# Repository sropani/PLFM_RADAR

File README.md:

# AERIS-10: Open Source Pulse Linear Frequency Modulated Phased Array Radar

AERIS-10 is an open-source, low-cost 10.5 GHz phased array radar system featuring Pulse Linear Frequency Modulated (LFM) modulation. Available in two versions (3km and 20km range), it's designed for researchers, drone developers, and serious SDR enthusiasts who want to explore and experiment with phased array radar technology.

## 📡 Overview

The AERIS-10 project aims to democratize radar technology by providing a fully open-source, modular, and hackable radar system. Whether you're a university researcher, a drone startup, or an advanced maker, AERIS-10 offers a platform for experimenting with beamforming, pulse compression, Doppler processing, and target tracking.

## 🔬 Key Features

- **Open Source Hardware & Software** - Complete schematics, PCB layouts, firmware, and software available
- **Dual Version Availability**:
  - **AERIS-10N (Nexus)**: 3km range with 8x16 patch antenna array
  - **AERIS-10E (Extended)**: 20km range with 32x16 dielectric-filled slotted waveguide array
- **Full Electronic Beam Steering** - ±45° electronic steering in elevation and azimuth
- **Advanced Signal Processing** - On-board FPGA handles pulse compression, Doppler FFT, MTI, and CFAR
- **Python GUI** - User-friendly interface with map integration
- **GPS/IMU Integration** - Real-time position and attitude correction
- **Modular Design** - Separate power management, frequency synthesis, and RF boards

## 🏗️ System Architecture

### Hardware Components

The AERIS-10 main sub-systems are:

- **Power Management Board** - Supplies all necessary voltage levels to the electronics components with proper filtering and sequencing (sequencing ensured by the microcontroller)

- **Frequency Synthesizer Board** - Uses a high-performance Low Jitter Clock Generator (AD9523-1) that supplies phase-aligned clock references for:
  - RX and TX Frequency Synthesizers (ADF4382)
  - DAC
  - ADC
  - FPGA

- **Main Board** containing:
  - **DAC** - Generates the RADAR Chirps
  - **2x Microwave Mixers (LT5552)** - For up-conversion and IF-down-conversion
  - **4x 4-Channel Phase Shifters (ADAR1000)** - For RX and TX chain beamforming
  - **16x Front End Chips (ADTR1107)** - Used for both Low Noise Amplifying (RX) and Power Amplifying (TX) stages
  - **XC7A50T FPGA** - Handles RADAR Signal Processing on the upstream FTG256 board:
    - PLFM Chirps generation via the DAC
    - Raw ADC data read
    - Automatic Gain Control (AGC)
    - I/Q Baseband Down-Conversion
    - Decimation
    - Filtering
    - Forward FFT
    - Pulse Compression
    - Doppler, MTI and CFAR processing
    - USB Interface
  - **STM32F746xx Microcontroller** - Used for:
    - Power-up and power-down sequencing (see Power Management Excel File)
    - FPGA communication
    - Setup and Interface with:
      - Clock Generator (AD9523-1)
      - 2x Frequency Synthesizers (ADF4382)
      - 4x 4-Channel Phase Shifters (ADAR1000) for RADAR pulse sequencing
      - 2x ADS7830 8-channel I²C ADCs (Main Board, U88 @ 0x48 / U89 @ 0x4A) for 16x Idq measurement, one per PA channel, each sensed through a 5 mΩ shunt on the PA board and an INA241A3 current-sense amplifier (x50) on the Main Board
      - 2x DAC5578 8-channel I²C DACs (Main Board, U7 @ 0x48 / U69 @ 0x49) for 16x Vg control, one per PA channel; closed-loop calibrated at boot to the target Idq
      - GPS module (UM982) for GUI map centering and per-detection position tagging
      - GY-85 IMU for pitch/roll correction of target coordinates
      - BMP180 Barometer
      - Stepper Motor
      - 1x ADS7830 8-channel I²C ADC (Main Board, U10) reading 8 thermistors for thermal monitoring; a single GPIO (EN_DIS_COOLING) switches the cooling fans on when any channel exceeds the threshold
      - RF switches

- **16x Power Amplifier Boards** - Used only for AERIS-10E version, featuring 10Watt QPA2962 GaN amplifier for extended range

- **Antenna Arrays**:
  - **AERIS-10N (Nexus)** - 8x16 patch antenna array
  - **AERIS-10X (Extended)** - 32x16 dielectric-filled slotted waveguide antenna array

- **Miscellaneous Components**:
  - Slip-Ring
  - Stepper Motor and drivers
  - Cooling Fans
  - Enclosure

### Processing Pipeline

1. **Waveform Generation** - DAC creates LFM chirps
2. **Up/Down Conversion** - LT5552 mixers handle frequency translation
3. **Beam Steering** - ADAR1000 phase shifters control 16 elements
4. **Signal Processing (FPGA)**:
   - Raw ADC data capture
   - I/Q baseband down-conversion
   - Decimation & filtering (CIC/FIR)
   - Pulse compression
   - Doppler FFT processing
   - MTI & CFAR detection
5. **System Management (STM32)**:
   - Power sequencing
   - Peripheral configuration
   - GPS/IMU integration
   - Stepper motor control
6. **Visualization (Python GUI)**:
   - Real-time target plotting
   - Map integration
   - Radar control interface

## 📊 Technical Specifications

| Parameter | AERIS-10N (Nexus) | AERIS-10X (Extended) |
|-----------|-------------------|----------------------|
| **Frequency** | 10.5 GHz | 10.5 GHz |
| **Max Range** | 3 km | 20 km |
| **Antenna** | 8x16 Patch Array | 32x16 Slotted Waveguide |
| **Beam Steering** | Electronic (±45°) | Electronic (±45°) |
| **Mechanical Scan** | 360° (stepper motor) | 360° (stepper motor) |
| **Output Power** | ~1W×16 | 10W×16 (GaN amplifier) |
| **Processing** | FPGA + STM32 | FPGA + STM32 |

## 🚀 Getting Started

### 🧹 Repository File Placement Policy

To keep the repository root clean and make artifacts easy to find, place generated files in the following locations:

- **Published reports (tracked, GitHub Pages):** `docs/`
  - Example: `docs/AERIS_Simulation_Report_v2.pdf`
- **Simulation-generated outputs (local, gitignored):** `5_Simulations/generated/`
  - Plots, scenario outputs, temporary analysis directories
- **FPGA/Vivado generated artifacts (local, gitignored):** `9_Firmware/9_2_FPGA/reports/`
  - VCD/VVP dumps, temporary CSVs, local report snapshots
- **Reusable FPGA automation scripts (tracked):** `9_Firmware/9_2_FPGA/scripts/`
  - TCL flows, helper scripts used by build/bring-up

**Do not leave generated artifacts in the repository root.**

### Prerequisites

- Basic understanding of radar principles
- Experience with PCB assembly (for hardware build)
- Python 3.8+ for the GUI software
- FPGA development tools (Vivado) for signal processing modifications

### Hardware Assembly

1. **Order PCBs**: Production outputs are under `/4_Schematics and Boards Layout/4_7_Production Files`
2. **Source Components**: BOM/CPL files are co-located under `/4_Schematics and Boards Layout/4_7_Production Files`
3. **Assembly**: Use the schematics in `/4_Schematics and Boards Layout/4_6_Schematics` together with the production outputs above; a standalone assembly guide is not currently tracked
4. **Antenna**: Choose appropriate array files for your target variant
5. **Enclosure**: Mechanical drawings currently live in `/8_Utils/Mechanical_Drawings`

## 📜 License

This project is open-source but uses **different licenses for hardware and software** to ensure proper legal coverage.

### Hardware Documentation
The hardware design files—including:
- Schematics and PCB layouts (in `/4_Schematics and Boards Layout`)
- Bill of Materials (BOM) files
- Gerber files and manufacturing outputs
- Mechanical drawings and enclosure designs

are licensed under the **CERN Open Hardware Licence Version 2 – Permissive (CERN-OHL-P)** .

This is a hardware-specific license that:
- ✅ Clearly defines "Hardware," "Documentation," and "Products"
- ✅ Includes explicit patent protection for contributors and users
- ✅ Provides stronger liability limitations (important for high-power RF)
- ✅ Aligns with professional open-hardware standards (CERN, OSHWA)

You may use, modify, and sell products based on these designs, provided you:
- Maintain the original copyright notices
- Distribute any modified designs under the same license
- Make your modifications available in Source format

### Software and Firmware
The software components—including:
- FPGA code (VHDL/Verilog in `/9_Firmware`)
- Microcontroller firmware (STM32)
- Python GUI and utilities

remain under the **MIT License** for maximum flexibility.

### Full License Texts
- The complete CERN-OHL-P license text is in the `LICENSE` file
- MIT license terms apply to software where not otherwise specified

### Why This Change?
Originally, the entire project used the MIT license. The community (special thanks to gmaynez!) pointed out that MIT lacks legal protections needed for physical hardware. The switch to CERN-OHL-P ensures the project is properly protected while maintaining the same permissive spirit.

## 📚 Documentation

Comprehensive documentation is available in the `/docs` folder and served via GitHub Pages at [https://NawfalMotii79.github.io/PLFM_RADAR/docs/](https://NawfalMotii79.github.io/PLFM_RADAR/docs/):

- [System Architecture](/docs/architecture.html)
- [Implementation Log](/docs/implementation-log.html)
- [Hardware Bring-Up Guide](/docs/bring-up.html)
- [Test Reports](/docs/reports.html)
- [Release Notes](/docs/release-notes.html)

## 🤝 Contributing

We welcome contributions! Please see our [Contributing Guidelines](/CONTRIBUTING.md) for details on repo layout, branch workflow, and basic PR checks.

Areas where help is especially appreciated:
- **RF Engineers**: Review designs, optimize antenna performance
- **FPGA Developers**: Optimize signal processing pipeline
- **Software Developers**: Enhance Python GUI and SDK
- **Beta Testers**: University researchers, drone startups, advanced makers

## 📞 Contact & Collaboration

I welcome serious inquiries from researchers, engineers, and potential collaborators. However, due to the high volume of interest in this project, please understand that I cannot guarantee a response to every message.

- **Technical questions or bug reports**: Please [open a GitHub issue](https://github.com/NawfalMotii79/PLFM_RADAR/issues) so the whole community can benefit from the discussion.
- **Collaboration, licensing, or business inquiries**: 📧 nawfal.motii.33 [at] gmail [dot] com

## 💰 Sponsors

---

**Star ⭐ this repository if you're interested in open-source radar technology!**

*Note: This is an active development project. Some features are still in progress. Check the issues page for known limitations and upcoming features.*

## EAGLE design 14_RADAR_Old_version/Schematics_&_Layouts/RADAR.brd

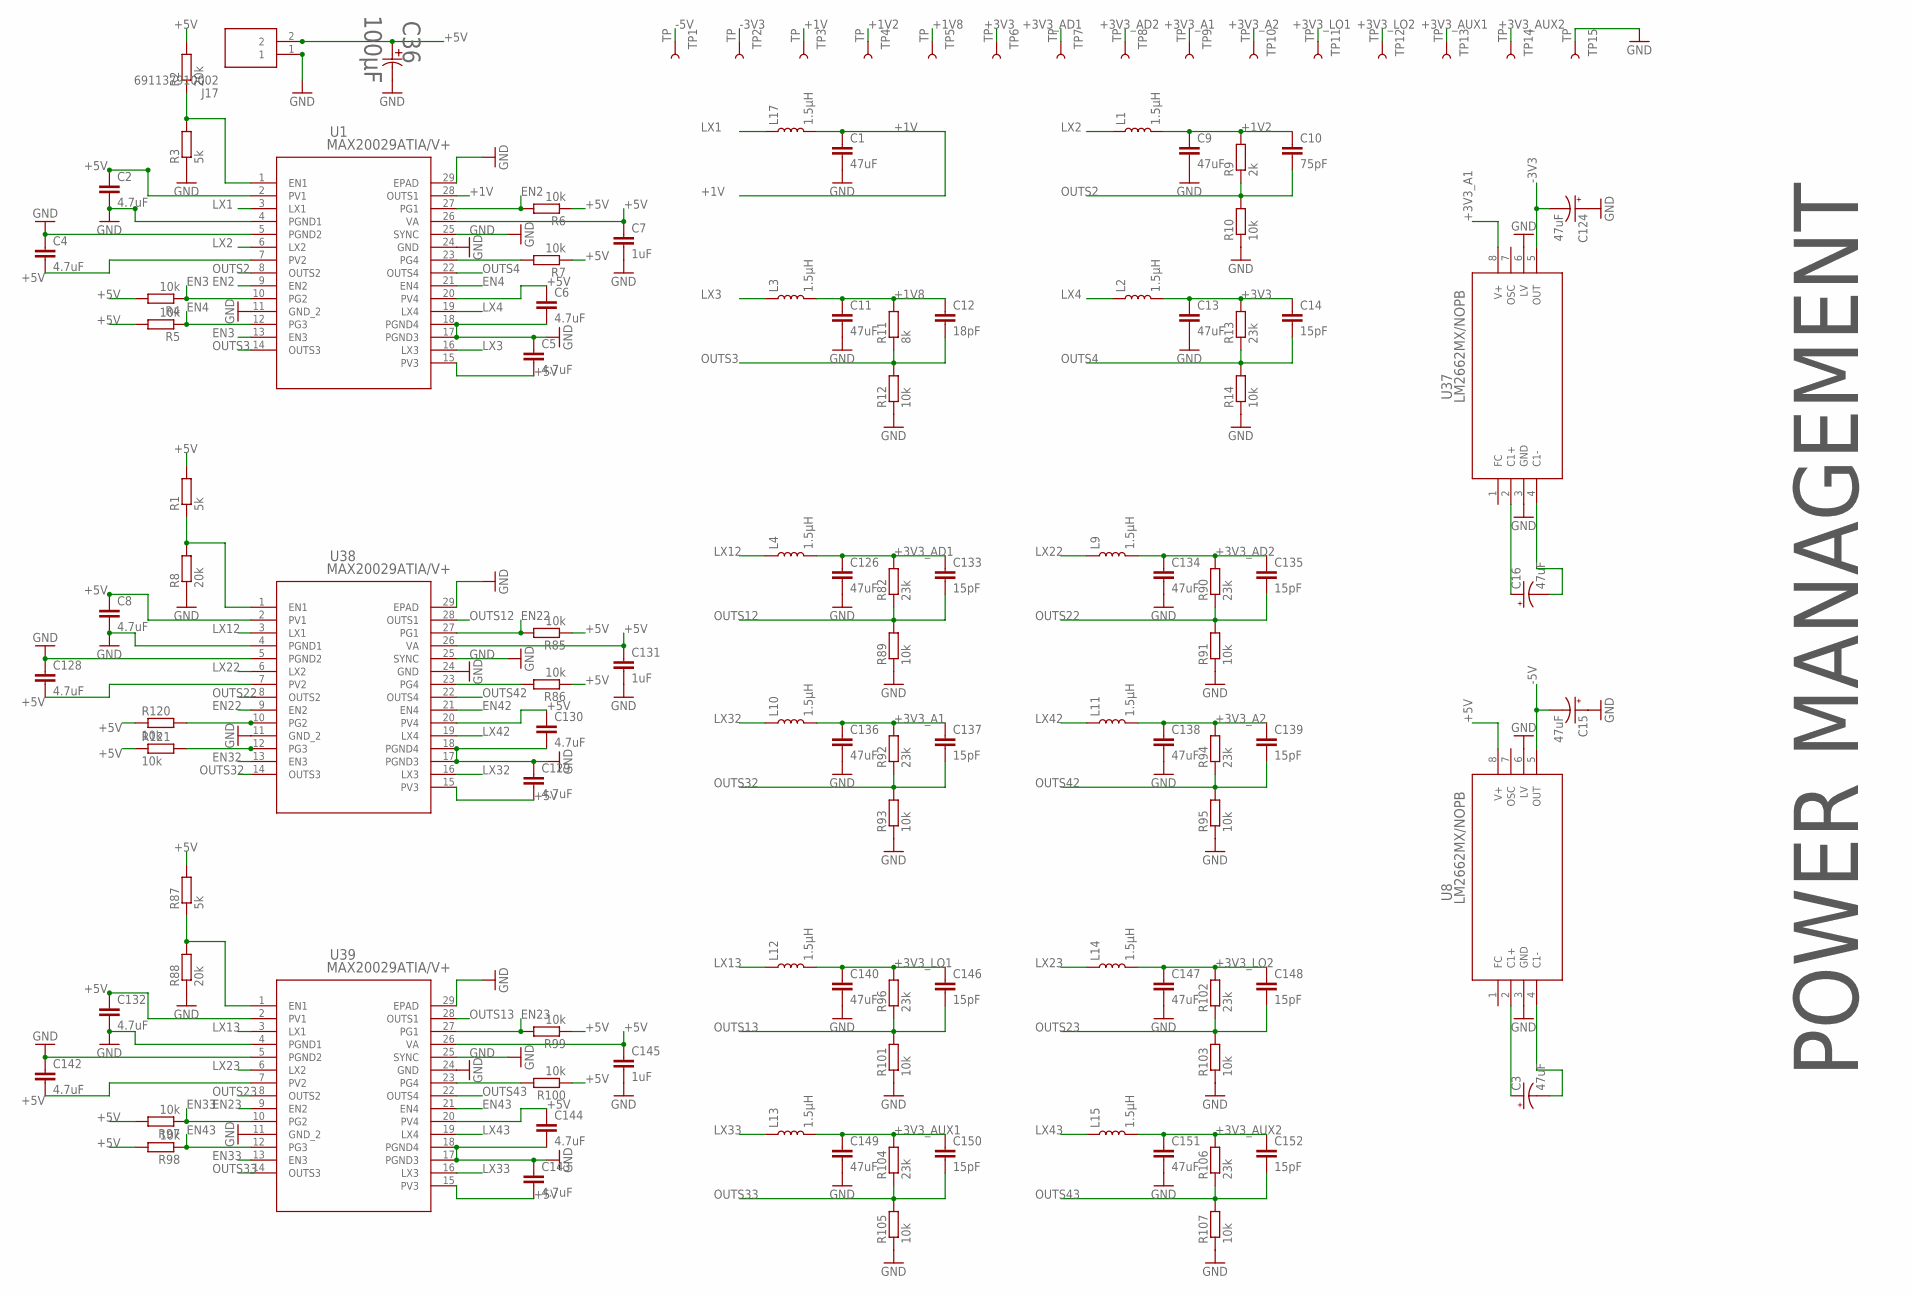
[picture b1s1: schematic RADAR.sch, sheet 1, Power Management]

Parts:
C1, C9, C11, C13, C126, C134, C136, C138, C140, C147, C149, C151: 47uF; C0201
C2, C4, C5, C6, C8, C128, C129, C130, C132, C142, C143, C144: 4.7uF; C0201
C3, C15, C16, C124: 47uF; 0603-POLAR
C7, C131, C145: 1uF; C0201
C10: 75pF; C0201
C12: 18pF; C0201
C14, C133, C135, C137, C139, C146, C148, C150, C152: 15pF; C0201
C36: 100µF; PCAP_8X10-ELECT_NCA
J17: 691137910002
L1, L2, L3, L4, L9, L10, L11, L12, L13, L14, L15, L17: 1.5µH; 0806
R1, R3, R87: 5k; R0201
R2, R8, R88: 20k; R0201
R4, R5, R6, R7, R10, R12, R14, R85, R86, R89, R91, R93, R95, R97, R98, R99, R100, R101, R103, R105, R107, R120, R121: 10k; R0201
R9: 2k; R0201
R11: 8k; R0201
R13, R82, R90, R92, R94, R96, R102, R104, R106: 23k; R0201
TP1, TP2, TP3, TP4, TP5, TP6, TP7, TP8, TP9, TP10, TP11, TP12, TP13, TP14, TP15: TP; PAD.02X.02
U1, U38, U39: MAX20029ATIA/V+; 21-0140L_T2855-5_MXM
U8, U37: LM2662MX/NOPB; M08A

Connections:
+1V: C1.1, L17.2, TP3.1, U1.28 (OUTS1); also elsewhere on the board
+1V2: C9.1, C10.1, L1.2, R9.2, TP4.1
+1V8: C11.1, C12.1, L3.2, R11.2, TP5.1; also elsewhere on the board
+3V3: C13.1, C14.1, L2.2, R13.2, TP6.1; also elsewhere on the board
+3V3_A1: C136.1, C137.1, L10.2, R92.2, TP9.1, U37.8 (V+); also elsewhere on the board
+3V3_A2: C138.1, C139.1, L11.2, R94.2, TP10.1; also elsewhere on the board
+3V3_AD1: C126.1, C133.1, L4.2, R82.2, TP7.1; also elsewhere on the board
+3V3_AD2: C134.1, C135.1, L9.2, R90.2, TP8.1; also elsewhere on the board
+3V3_AUX1: C149.1, C150.1, L13.2, R104.2, TP13.1
+3V3_AUX2: C151.1, C152.1, L15.2, R106.2, TP14.1
+3V3_LO1: C140.1, C146.1, L12.2, R96.2, TP11.1; also elsewhere on the board
+3V3_LO2: C147.1, C148.1, L14.2, R102.2, TP12.1; also elsewhere on the board
+5V: C2.1, C4.2, C5.2, C6.1, C7.1, C8.1, C36.1, C128.2, C129.2, C130.1, C131.1, C132.1, C142.2, C143.2, C144.1, C145.1, J17.2, R1.2, R2.2, R4.2, R5.2, R6.1, R7.1, R85.1, R86.1, R87.2, R97.2, R98.2, R99.1, R100.1, R120.1, R121.1, U1.2 (PV1), U1.7 (PV2), U1.15 (PV3), U1.20 (PV4), U1.26 (VA), U8.8 (V+), U38.2 (PV1), U38.7 (PV2), U38.15 (PV3), U38.20 (PV4), U38.26 (VA), U39.2 (PV1), U39.7 (PV2), U39.15 (PV3), U39.20 (PV4), U39.26 (VA); also elsewhere on the board
-3V3: C124.-, TP2.1, U37.5 (OUT); also elsewhere on the board
-5V: C15.-, TP1.1, U8.5 (OUT); also elsewhere on the board
EN2: R6.2, U1.9 (EN2), U1.27 (PG1)
EN3: R4.1, U1.10 (PG2), U1.13 (EN3)
EN4: R5.1, U1.12 (PG3), U1.21 (EN4)
EN22: R85.2, U38.9 (EN2), U38.27 (PG1)
EN23: R99.2, U39.9 (EN2), U39.27 (PG1)
EN32: U38.13 (EN3); also elsewhere on the board
EN33: R97.1, U39.10 (PG2), U39.13 (EN3)
EN42: U38.21 (EN4); also elsewhere on the board
EN43: R98.1, U39.12 (PG3), U39.21 (EN4)
GND: C1.2, C2.2, C4.1, C5.1, C6.2, C7.2, C8.2, C9.2, C11.2, C13.2, C15.+, C36.2, C124.+, C126.2, C128.1, C129.1, C130.2, C131.2, C132.2, C134.2, C136.2, C138.2, C140.2, C142.1, C143.1, C144.2, C145.2, C147.2, C149.2, C151.2, J17.1, R3.1, R8.1, R10.1, R12.1, R14.1, R88.1, R89.1, R91.1, R93.1, R95.1, R101.1, R103.1, R105.1, R107.1, TP15.1, U1.4 (PGND1), U1.5 (PGND2), U1.11 (GND_2), U1.17 (PGND3), U1.18 (PGND4), U1.24 (GND), U1.25 (SYNC), U1.29 (EPAD), U8.3 (GND), U8.6 (LV), U37.3 (GND), U37.6 (LV), U38.4 (PGND1), U38.5 (PGND2), U38.11 (GND_2), U38.17 (PGND3), U38.18 (PGND4), U38.24 (GND), U38.25 (SYNC), U38.29 (EPAD), U39.4 (PGND1), U39.5 (PGND2), U39.11 (GND_2), U39.17 (PGND3), U39.18 (PGND4), U39.24 (GND), U39.25 (SYNC), U39.29 (EPAD); also elsewhere on the board
LX1: L17.1, U1.3 (LX1)
LX2: L1.1, U1.6 (LX2)
LX3: L3.1, U1.16 (LX3)
LX4: L2.1, U1.19 (LX4)
LX12: L4.1, U38.3 (LX1)
LX13: L12.1, U39.3 (LX1)
LX22: L9.1, U38.6 (LX2)
LX23: L14.1, U39.6 (LX2)
LX32: L10.1, U38.16 (LX3)
LX33: L13.1, U39.16 (LX3)
LX42: L11.1, U38.19 (LX4)
LX43: L15.1, U39.19 (LX4)
unnamed: R2.1, R3.2, U1.1 (EN1)
unnamed: C3.+, U8.2 (C1+)
unnamed: C3.-, U8.4 (C1-)
unnamed: R7.2, U1.23 (PG4)
unnamed: C16.+, U37.2 (C1+)
unnamed: C16.-, U37.4 (C1-)
unnamed: R1.1, R8.2, U38.1 (EN1)
unnamed: R86.2, U38.23 (PG4)
unnamed: R87.1, R88.2, U39.1 (EN1)
unnamed: R100.2, U39.23 (PG4)
OUTS2: C10.2, R9.1, R10.2, U1.8 (OUTS2)
OUTS3: C12.2, R11.1, R12.2, U1.14 (OUTS3)
OUTS4: C14.2, R13.1, R14.2, U1.22 (OUTS4)
OUTS12: C133.2, R82.1, R89.2, U38.28 (OUTS1)
OUTS13: C146.2, R96.1, R101.2, U39.28 (OUTS1)
OUTS22: C135.2, R90.1, R91.2, U38.8 (OUTS2)
OUTS23: C148.2, R102.1, R103.2, U39.8 (OUTS2)
OUTS32: C137.2, R92.1, R93.2, U38.14 (OUTS3)
OUTS33: C150.2, R104.1, R105.2, U39.14 (OUTS3)
OUTS42: C139.2, R94.1, R95.2, U38.22 (OUTS4)
OUTS43: C152.2, R106.1, R107.2, U39.22 (OUTS4)
PG22: R120.2, U38.10 (PG2)
PG32: R121.2, U38.12 (PG3)

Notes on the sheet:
POWER MANAGEMENT

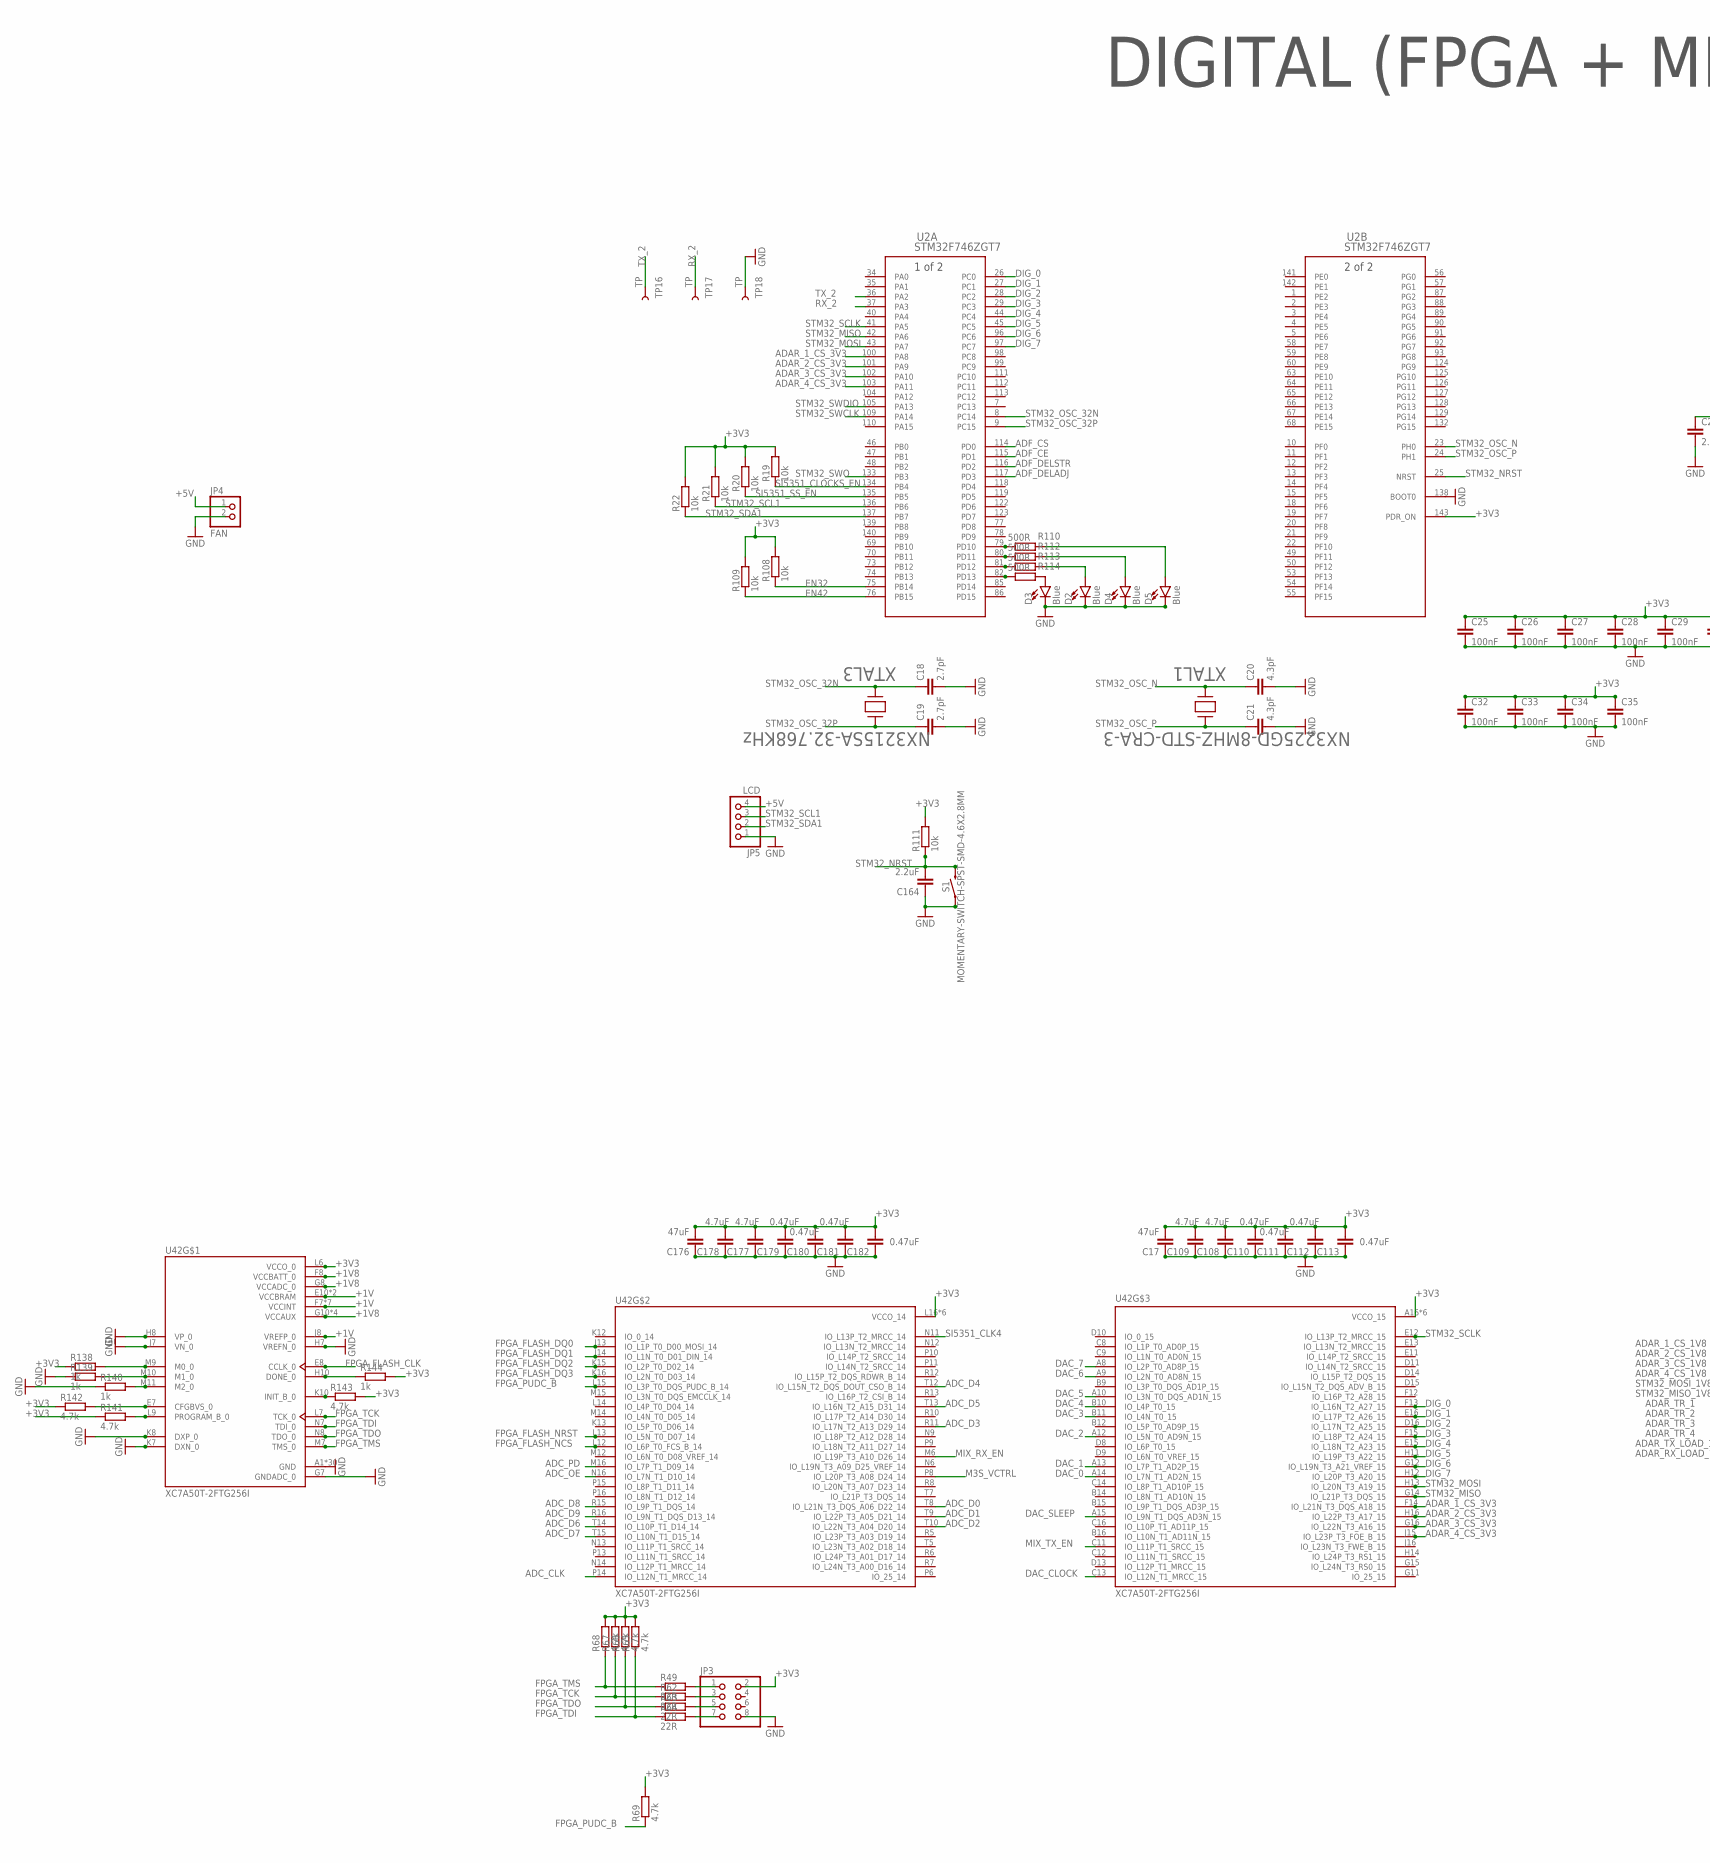
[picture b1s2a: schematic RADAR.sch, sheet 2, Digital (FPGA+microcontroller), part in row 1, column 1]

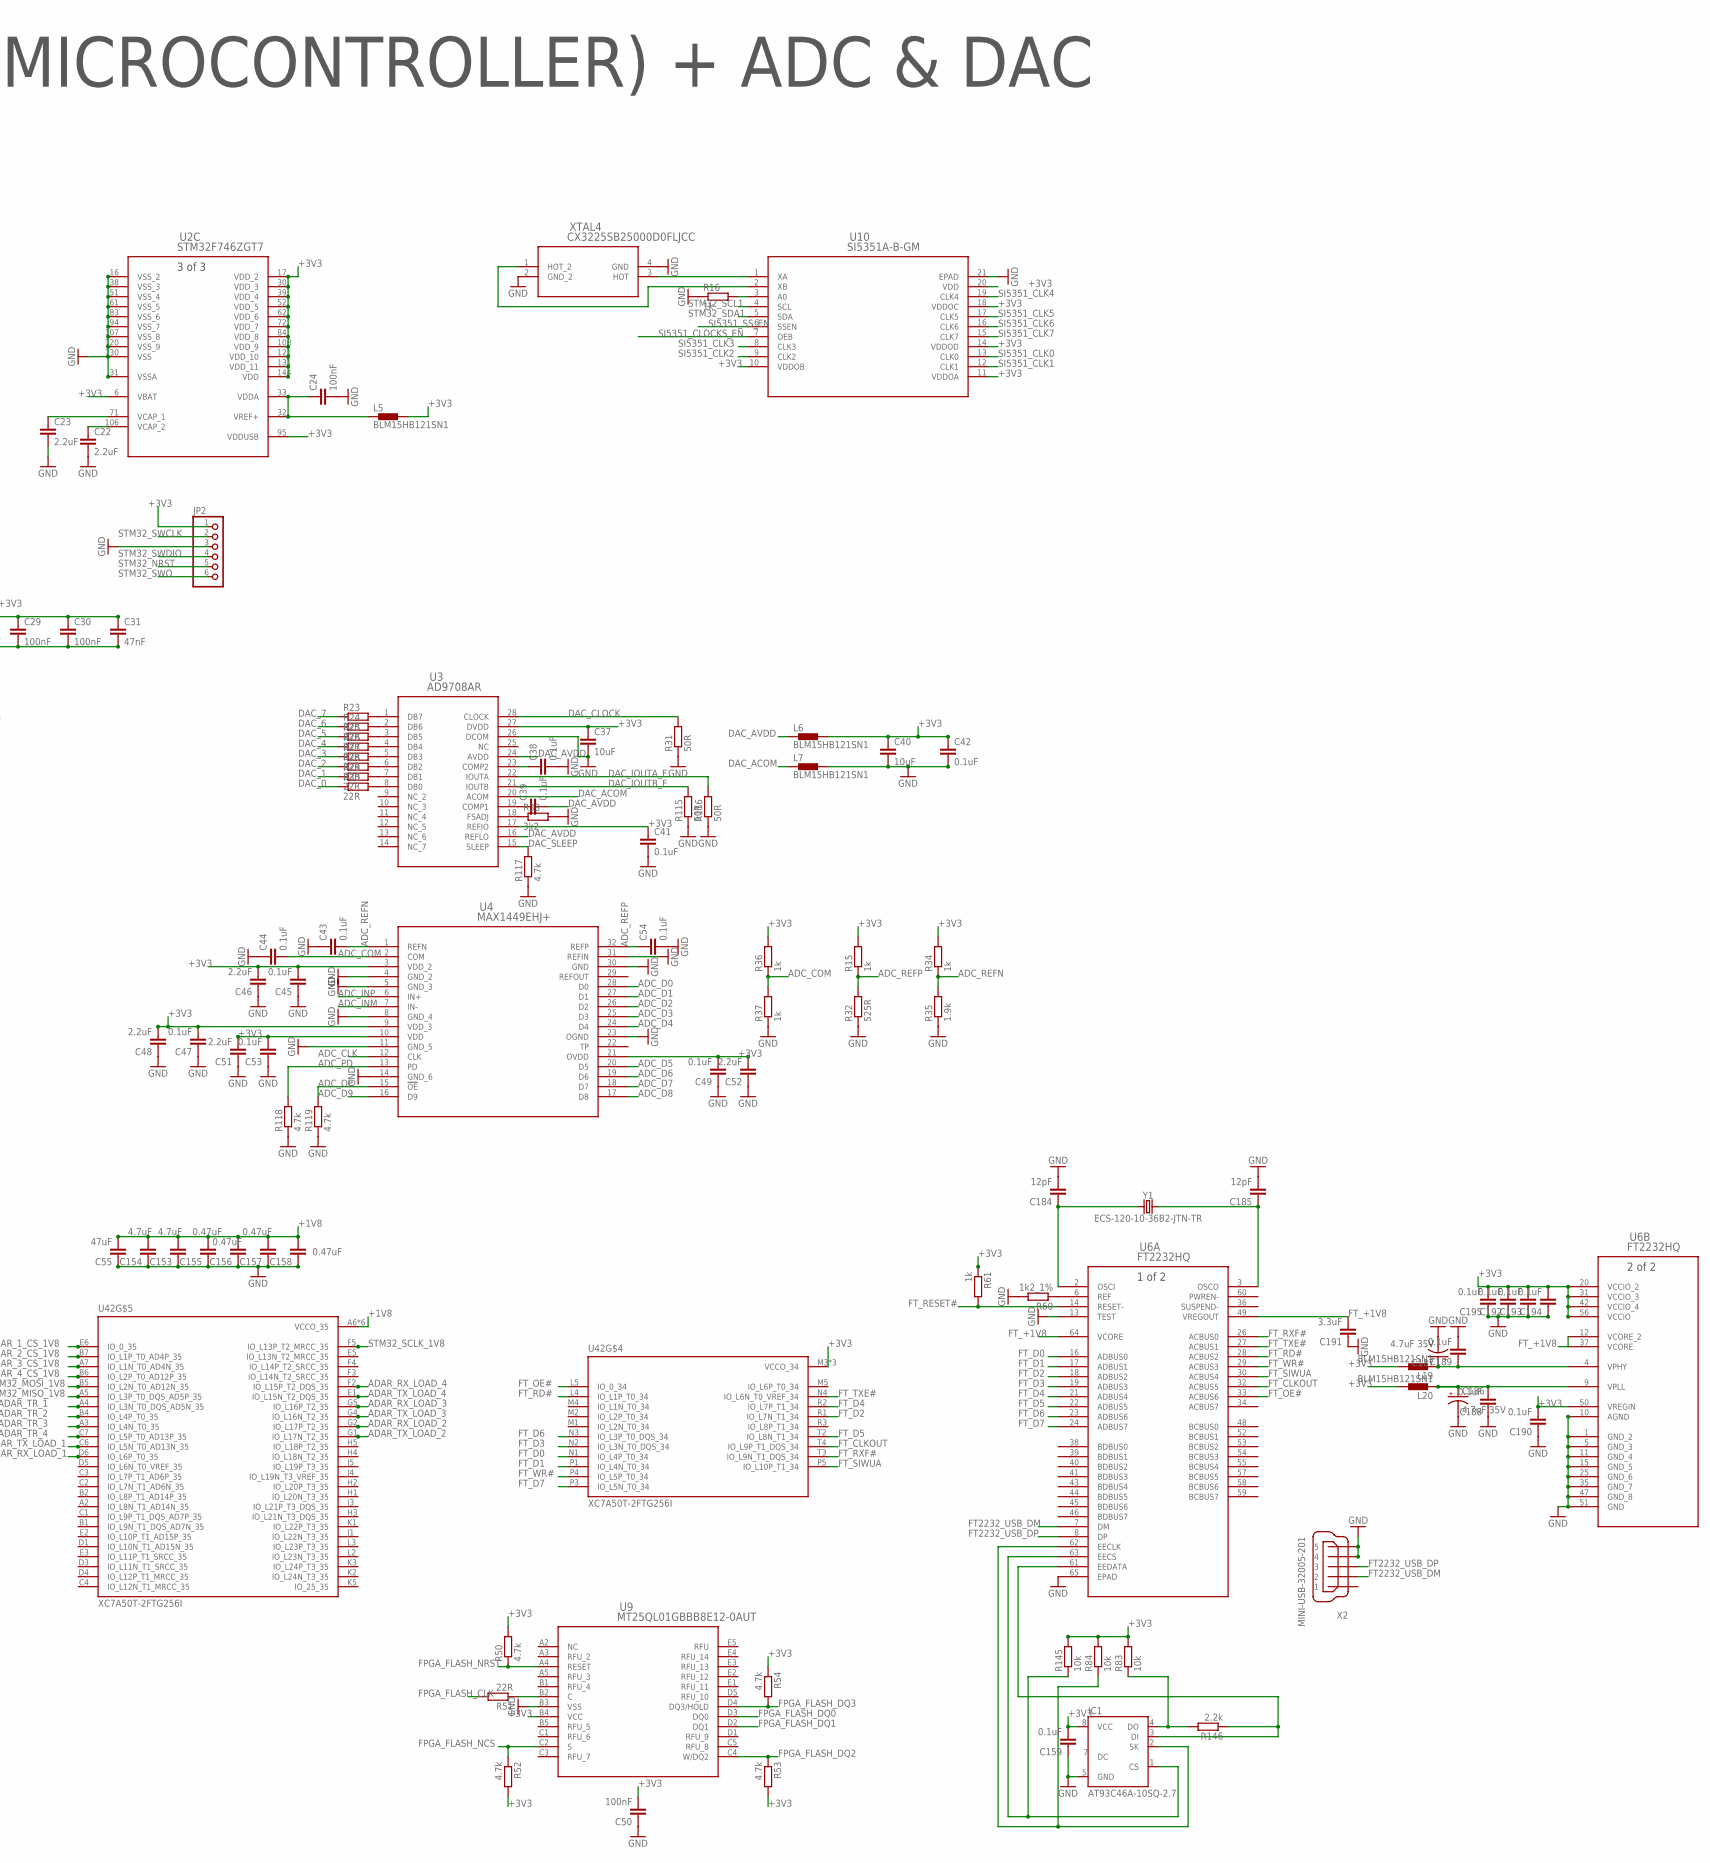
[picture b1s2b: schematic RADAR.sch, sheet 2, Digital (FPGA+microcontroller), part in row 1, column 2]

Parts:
C17, C55, C176: 47uF; C0201
C18, C19: 2.7pF; C0201
C20, C21: 4.3pF; C0201
C22, C23, C46, C48, C51, C52, C164: 2.2uF; C0201
C24, C25, C26, C27, C28, C29, C30, C32, C33, C34, C35, C50: 100nF; C0201
C31: 47nF; C0201
C37, C40: 10uF; C0201
C38, C39, C41, C42, C43, C44, C45, C47, C49, C53, C54, C159, C188, C189, C190, C192, C193, C194, C195: 0.1uF; C0201
C108, C109, C153, C154, C177, C178: 4.7uF; C0201
C110, C111, C112, C113, C155, C156, C157, C158, C179, C180, C181, C182: 0.47uF; C0201
C184, C185: 12pF; C0201
C186, C187: 4.7uF 35V; EIA3528
C191: 3.3uF; C0201
D2, D3, D4, D5: Blue; LED-0603
IC1: AT93C46A-10SQ-2.7; SOIC8
JP2: PINHD-1X6; 1X06
JP3: PINHD-2X4; 2X04
JP4: FAN; 1X02
JP5: LCD; 1X04
L5, L6, L7, L19, L20: BLM15HB121SN1; 0402
R15, R16, R34, R36, R37, R61, R138, R139, R140, R144: 1k; R0201
R19, R20, R21, R22, R83, R84, R108, R109, R111, R145: 10k; R0201
R23, R24, R25, R26, R27, R28, R29, R30, R49, R51, R62, R63, R64: 22R; R0201
R31, R115, R116: 50R; R0201
R32: 525R; R0201
R33: 3k2; R0201
R35: 1.9k; R0201
R50, R52, R53, R54, R65, R66, R67, R68, R69, R117, R118, R119, R141, R142, R143: 4.7k; R0201
R60: 1k2_1%; R0201
R110, R112, R113, R114: 500R; R0201
R146: 2.2k; R0201
S1: MOMENTARY-SWITCH-SPST-SMD-4.6X2.8MM; TACTILE_SWITCH_SMD_4.6X2.8MM
TP16, TP17, TP18: TP; PAD.02X.02
U2: STM32F746ZGT7; LQFP-144_STM
U3: AD9708AR; RW_28_ADI
U4: MAX1449EHJ+; 21-0110B_MXM
U6: FT2232HQ; 64QFN_FT2232HQ_FTD
U9: MT25QL01GBBB8E12-0AUT; BGA24_MT25QL_MRN
U10: SI5351A-B-GM; QFN20_SIL
U42: XC7A50T-2FTG256I; BGA256C100P16X16_1700X1700X155
X2: MINI-USB-32005-201; 32005-201
XTAL1: NX3225GD-8MHZ-STD-CRA-3; XTAL_NX3225GD-8MHZ-STD-CRA-3_N
XTAL3: NX3215SA-32.768KHz; XTAL_NX3225GD-8MHZ-STD-CRA-3_N
XTAL4: CX3225SB25000D0FLJCC; XTAL4_CX3225SB_AVX
Y1: ECS-120-10-36B2-JTN-TR; CRYSTAL-SMD-2X2.5MM

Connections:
+1V: U42.E10 (VCCBRAM), U42.F7 (VCCINT), U42.F9 (VCCINT), U42.F11 (VCCBRAM), U42.G6 (VCCINT), U42.H9 (VCCINT), U42.J6 (VCCINT), U42.J8 (VREFP_0), U42.K9 (VCCINT), U42.L8 (VCCINT); also elsewhere on the board
+1V8: C55.2, C153.2, C154.2, C155.2, C156.2, C157.2, C158.2, U42.A6 (VCCO_35), U42.B3 (VCCO_35), U42.D7 (VCCO_35), U42.E4 (VCCO_35), U42.F1 (VCCO_35), U42.F8 (VCCBATT_0), U42.G8 (VCCADC_0), U42.G10 (VCCAUX), U42.J2 (VCCO_35), U42.J10 (VCCAUX), U42.K11 (VCCAUX), U42.L10 (VCCAUX); also elsewhere on the board
+3V3: C17.2, C25.1, C26.1, C27.1, C28.1, C29.1, C30.1, C31.1, C32.1, C33.1, C34.1, C35.1, C37.1, C40.1, C41.1, C42.1, C45.2, C46.2, C47.2, C48.2, C49.2, C50.2, C51.2, C52.2, C53.2, C108.2, C109.2, C110.2, C111.2, C112.2, C113.2, C159.2, C176.2, C177.2, C178.2, C179.2, C180.2, C181.2, C182.2, C190.2, C192.2, C193.2, C194.2, C195.2, IC1.8 (VCC), JP2.1, JP3.2, L5.2, L6.2, L19.2, L20.2, R15.2, R19.2, R20.2, R21.2, R22.2, R34.2, R36.2, R50.2, R52.2, R53.2, R54.1, R61.1, R65.2, R66.2, R67.2, R68.2, R69.2, R83.2, R84.2, R108.2, R109.2, R111.2, R138.1, R141.1, R142.1, R143.2, R144.2, R145.2, U2.6 (VBAT), U2.17 (VDD_2), U2.30 (VDD_3), U2.39 (VDD_4), U2.52 (VDD_5), U2.62 (VDD_6), U2.72 (VDD_7), U2.84 (VDD_8), U2.95 (VDDUSB), U2.108 (VDD_9), U2.121 (VDD_10), U2.131 (VDD_11), U2.143 (PDR_ON), U2.144 (VDD), U3.17 (REFIO), U3.27 (DVDD), U4.3 (VDD_2), U4.9 (VDD_3), U4.10 (VDD), U4.21 (OVDD), U6.20 (VCCIO_2), U6.31 (VCCIO_3), U6.42 (VCCIO_4), U6.50 (VREGIN), U6.56 (VCCIO), U9.B4 (VCC), U10.10 (VDDOB), U10.11 (VDDOA), U10.14 (VDDOD), U10.18 (VDDOC), U10.20 (VDD), U42.A16 (VCCO_15), U42.B13 (VCCO_15), U42.C10 (VCCO_15), U42.E14 (VCCO_15), U42.H15 (VCCO_15), U42.J12 (VCCO_15), U42.L6 (VCCO_0), U42.L16 (VCCO_14), U42.M3 (VCCO_34), U42.M13 (VCCO_14), U42.N10 (VCCO_14), U42.P7 (VCCO_14), U42.R4 (VCCO_34), U42.R14 (VCCO_14), U42.T1 (VCCO_34), U42.T11 (VCCO_14); also elsewhere on the board
+5V: JP4.1, JP5.4; also elsewhere on the board
ADAR_1_CS_1V8: U42.E6 (IO_0_35); also elsewhere on the board
ADAR_1_CS_3V3: U2.100 (PA8), U42.F14 (IO_L21N_T3_DQS_A18_15)
ADAR_2_CS_1V8: U42.B7 (IO_L1P_T0_AD4P_35); also elsewhere on the board
ADAR_2_CS_3V3: U2.101 (PA9), U42.H16 (IO_L22P_T3_A17_15)
ADAR_3_CS_1V8: U42.A7 (IO_L1N_T0_AD4N_35); also elsewhere on the board
ADAR_3_CS_3V3: U2.102 (PA10), U42.G16 (IO_L22N_T3_A16_15)
ADAR_4_CS_1V8: U42.B6 (IO_L2P_T0_AD12P_35); also elsewhere on the board
ADAR_4_CS_3V3: U2.103 (PA11), U42.J15 (IO_L23P_T3_FOE_B_15)
ADAR_RX_LOAD_1: U42.D6 (IO_L6P_T0_35); also elsewhere on the board
ADAR_RX_LOAD_2: U42.G2 (IO_L17P_T2_35); also elsewhere on the board
ADAR_RX_LOAD_3: U42.G5 (IO_L16P_T2_35); also elsewhere on the board
ADAR_RX_LOAD_4: U42.F2 (IO_L15P_T2_DQS_35); also elsewhere on the board
ADAR_TR_1: U42.A4 (IO_L3N_T0_DQS_AD5N_35); also elsewhere on the board
ADAR_TR_2: U42.B4 (IO_L4P_T0_35); also elsewhere on the board
ADAR_TR_3: U42.A3 (IO_L4N_T0_35); also elsewhere on the board
ADAR_TR_4: U42.C7 (IO_L5P_T0_AD13P_35); also elsewhere on the board
ADAR_TX_LOAD_1: U42.C6 (IO_L5N_T0_AD13N_35); also elsewhere on the board
ADAR_TX_LOAD_2: U42.G1 (IO_L17N_T2_35); also elsewhere on the board
ADAR_TX_LOAD_3: U42.G4 (IO_L16N_T2_35); also elsewhere on the board
ADAR_TX_LOAD_4: U42.E1 (IO_L15N_T2_DQS_35); also elsewhere on the board
ADC_CLK: U4.12 (CLK), U42.P14 (IO_L12N_T1_MRCC_14)
ADC_COM: C44.2, R36.1, R37.2, U4.2 (COM); also elsewhere on the board
ADC_D0: U4.28 (D0), U42.T8 (IO_L21N_T3_DQS_A06_D22_14)
ADC_D1: U4.27 (D1), U42.T9 (IO_L22P_T3_A05_D21_14)
ADC_D2: U4.26 (D2), U42.T10 (IO_L22N_T3_A04_D20_14)
ADC_D3: U4.25 (D3), U42.R11 (IO_L17N_T2_A13_D29_14)
ADC_D4: U4.24 (D4), U42.T12 (IO_L15N_T2_DQS_DOUT_CSO_B_14)
ADC_D5: U4.20 (D5), U42.T13 (IO_L16N_T2_A15_D31_14)
ADC_D6: U4.19 (D6), U42.T14 (IO_L10P_T1_D14_14)
ADC_D7: U4.18 (D7), U42.T15 (IO_L10N_T1_D15_14)
ADC_D8: U4.17 (D8), U42.R15 (IO_L9P_T1_DQS_14)
ADC_D9: U4.16 (D9), U42.R16 (IO_L9N_T1_DQS_D13_14)
ADC_INM: U4.7 (IN-); also elsewhere on the board
ADC_INP: U4.6 (IN+); also elsewhere on the board
ADC_OE: R119.2, U4.15 (!OE), U42.N16 (IO_L7N_T1_D10_14)
ADC_PD: R118.2, U4.13 (PD), U42.M16 (IO_L7P_T1_D09_14)
ADC_REFN: C43.2, R34.1, R35.2, U4.1 (REFN)
ADC_REFP: C54.1, R15.1, R32.2, U4.32 (REFP)
ADF_CE: U2.115 (PD1); also elsewhere on the board
ADF_CS: U2.114 (PD0); also elsewhere on the board
ADF_DELADJ: U2.117 (PD3); also elsewhere on the board
ADF_DELSTR: U2.116 (PD2); also elsewhere on the board
DAC_0: R30.1, U42.A14 (IO_L7N_T1_AD2N_15)
DAC_1: R29.1, U42.A13 (IO_L7P_T1_AD2P_15)
DAC_2: R28.1, U42.A12 (IO_L5N_T0_AD9N_15)
DAC_3: R27.1, U42.B11 (IO_L4N_T0_15)
DAC_4: R26.1, U42.B10 (IO_L4P_T0_15)
DAC_5: R25.1, U42.A10 (IO_L3N_T0_DQS_AD1N_15)
DAC_6: R24.1, U42.A9 (IO_L2N_T0_AD8N_15)
DAC_7: R23.1, U42.A8 (IO_L2P_T0_AD8P_15)
DAC_ACOM: L7.1, U3.20 (ACOM)
DAC_AVDD: C39.2, L6.1, U3.16 (REFLO), U3.24 (AVDD)
DAC_CLOCK: R31.2, U3.28 (CLOCK), U42.C13 (IO_L12N_T1_MRCC_15)
DAC_IOUTA_F: R116.2, U3.22 (IOUTA); also elsewhere on the board
DAC_IOUTB_F: R115.2, U3.21 (IOUTB); also elsewhere on the board
DAC_SLEEP: R117.2, U3.15 (SLEEP), U42.A15 (IO_L9N_T1_DQS_AD3N_15)
DIG_0: U2.26 (PC0), U42.F13 (IO_L16N_T2_A27_15)
DIG_1: U2.27 (PC1), U42.E16 (IO_L17P_T2_A26_15)
DIG_2: U2.28 (PC2), U42.D16 (IO_L17N_T2_A25_15)
DIG_3: U2.29 (PC3), U42.F15 (IO_L18P_T2_A24_15)
DIG_4: U2.44 (PC4), U42.E15 (IO_L18N_T2_A23_15)
DIG_5: U2.45 (PC5), U42.H11 (IO_L19P_T3_A22_15)
DIG_6: U2.96 (PC6), U42.G12 (IO_L19N_T3_A21_VREF_15)
DIG_7: U2.97 (PC7), U42.H12 (IO_L20P_T3_A20_15)
EN32: R108.1, U2.75 (PB14); also elsewhere on the board
EN42: R109.1, U2.76 (PB15); also elsewhere on the board
FPGA_FLASH_CLK: R51.2, U42.E8 (CCLK_0)
FPGA_FLASH_DQ0: U9.D3 (DQ0), U42.J13 (IO_L1P_T0_D00_MOSI_14)
FPGA_FLASH_DQ1: U9.D2 (DQ1), U42.J14 (IO_L1N_T0_D01_DIN_14)
FPGA_FLASH_DQ2: R53.1, U9.C4 (W/DQ2), U42.K15 (IO_L2P_T0_D02_14)
FPGA_FLASH_DQ3: R54.2, U9.D4 (DQ3/HOLD), U42.K16 (IO_L2N_T0_D03_14)
FPGA_FLASH_NCS: R52.1, U9.C2 (S), U42.L12 (IO_L6P_T0_FCS_B_14)
FPGA_FLASH_NRST: R50.1, U9.A4 (RESET), U42.L13 (IO_L5N_T0_D07_14)
FPGA_PUDC_B: R69.1, U42.L15 (IO_L3P_T0_DQS_PUDC_B_14)
FPGA_TCK: R62.1, R67.1, U42.L7 (TCK_0)
FPGA_TDI: R64.1, R65.1, U42.N7 (TDI_0)
FPGA_TDO: R63.1, R66.1, U42.N8 (TDO_0)
FPGA_TMS: R49.1, R68.1, U42.M7 (TMS_0)
FT2232_USB_DM: U6.7 (DM), X2.2
FT2232_USB_DP: U6.8 (DP), X2.3
FT_+1V8: C191.2, U6.12 (VCORE_2), U6.37 (VCORE), U6.49 (VREGOUT), U6.64 (VCORE)
FT_CLKOUT: U6.32 (ACBUS5), U42.T4 (IO_L9P_T1_DQS_34)
FT_D0: U6.16 (ADBUS0), U42.N1 (IO_L4P_T0_34)
FT_D1: U6.17 (ADBUS1), U42.P1 (IO_L4N_T0_34)
FT_D2: U6.18 (ADBUS2), U42.R1 (IO_L7N_T1_34)
FT_D3: U6.19 (ADBUS3), U42.N2 (IO_L3N_T0_DQS_34)
FT_D4: U6.21 (ADBUS4), U42.R2 (IO_L7P_T1_34)
FT_D5: U6.22 (ADBUS5), U42.T2 (IO_L8N_T1_34)
FT_D6: U6.23 (ADBUS6), U42.N3 (IO_L3P_T0_DQS_34)
FT_D7: U6.24 (ADBUS7), U42.P3 (IO_L5N_T0_34)
FT_OE#: U6.33 (ACBUS6), U42.L5 (IO_0_34)
FT_RD#: U6.28 (ACBUS2), U42.L4 (IO_L1P_T0_34)
FT_RESET#: R61.2, U6.14 (RESET-)
FT_RXF#: U6.26 (ACBUS0), U42.T3 (IO_L9N_T1_DQS_34)
FT_SIWUA: U6.30 (ACBUS4), U42.P5 (IO_L10P_T1_34)
FT_TXE#: U6.27 (ACBUS1), U42.N4 (IO_L6N_T0_VREF_34)
FT_WR#: U6.29 (ACBUS3), U42.P4 (IO_L5P_T0_34)
GND: C17.1, C18.2, C19.2, C20.2, C21.2, C22.2, C23.2, C24.2, C25.2, C26.2, C27.2, C28.2, C29.2, C30.2, C31.2, C32.2, C33.2, C34.2, C35.2, C37.2, C38.2, C40.2, C41.2, C42.2, C43.1, C44.1, C45.1, C46.1, C47.1, C48.1, C49.1, C50.1, C51.1, C52.1, C53.1, C54.2, C55.1, C108.1, C109.1, C110.1, C111.1, C112.1, C113.1, C153.1, C154.1, C155.1, C156.1, C157.1, C158.1, C159.1, C164.1, C176.1, C177.1, C178.1, C179.1, C180.1, C181.1, C182.1, C184.2, C185.2, C186.C (-), C187.C (-), C188.1, C189.2, C190.1, C191.1, C192.1, C193.1, C194.1, C195.1, D2.C, D3.C, D4.C, D5.C, IC1.5 (GND), JP2.3, JP3.8, JP4.2, JP5.1, L7.2, R16.1, R31.1, R32.1, R33.2, R35.1, R37.1, R60.2, R115.1, R116.1, R117.1, R118.1, R119.1, R139.1, R140.1, S1.1, S1.2 (1), TP18.1, U2.16 (VSS_2), U2.31 (VSSA), U2.38 (VSS_3), U2.51 (VSS_4), U2.61 (VSS_5), U2.83 (VSS_6), U2.94 (VSS_7), U2.107 (VSS_8), U2.120 (VSS_9), U2.130 (VSS), U2.138 (BOOT0), U3.26 (DCOM), U4.4 (GND_2), U4.5 (GND_3), U4.8 (GND_4), U4.11 (GND_5), U4.14 (GND_6), U4.23 (OGND), U4.30 (GND), U4.31 (REFIN), U6.1 (GND_2), U6.5 (GND_3), U6.10 (AGND), U6.11 (GND_4), U6.13 (TEST), U6.15 (GND_5), U6.25 (GND_6), U6.35 (GND_7), U6.47 (GND_8), U6.51 (GND), U6.65 (EPAD), U9.B3 (VSS), U10.21 (EPAD), U42.A1 (GND), U42.A11 (GND), U42.B8 (GND), U42.C5 (GND), U42.C15 (GND), U42.D2 (GND), U42.D12 (GND), U42.E9 (GND), U42.F6 (GND), U42.F10 (GND), U42.F16 (GND), U42.G3 (GND), U42.G7 (GNDADC_0), U42.G9 (GND), U42.G13 (GND), U42.H6 (GND), U42.H7 (VREFN_0), U42.H8 (VP_0), U42.J7 (VN_0), U42.J9 (GND), U42.J11 (GND), U42.K4 (GND), U42.K6 (GND), U42.K7 (DXN_0), U42.K8 (DXP_0), U42.K14 (GND), U42.L1 (GND), U42.L11 (GND), U42.M8 (GND), U42.N5 (GND), U42.N15 (GND), U42.P2 (GND), U42.P12 (GND), U42.R9 (GND), U42.T6 (GND), U42.T16 (GND), X2.4, X2.5, XTAL4.2 (GND_2), XTAL4.4 (GND); also elsewhere on the board
M3S_VCTRL: U42.P8 (IO_L20P_T3_A08_D24_14); also elsewhere on the board
MIX_RX_EN: U42.M6 (IO_L19P_T3_A10_D26_14); also elsewhere on the board
MIX_TX_EN: U42.C11 (IO_L11P_T1_SRCC_15); also elsewhere on the board
unnamed: U10.1 (XA), XTAL4.3 (HOT)
unnamed: U10.2 (XB), XTAL4.1 (HOT_2)
unnamed: R16.2, U10.3 (A0)
unnamed: C23.1, U2.71 (VCAP_1)
unnamed: C22.1, U2.106 (VCAP_2)
unnamed: C24.1, L5.1, U2.32 (VREF+), U2.33 (VDDA)
unnamed: R23.2, U3.1 (DB7)
unnamed: R24.2, U3.2 (DB6)
unnamed: R25.2, U3.3 (DB5)
unnamed: R26.2, U3.4 (DB4)
unnamed: R27.2, U3.5 (DB3)
unnamed: R28.2, U3.6 (DB2)
unnamed: R29.2, U3.7 (DB1)
unnamed: R30.2, U3.8 (DB0)
unnamed: R33.1, U3.18 (FSADJ)
unnamed: R51.1, U9.B2 (C)
unnamed: JP3.1, R49.2
unnamed: JP3.3, R62.2
unnamed: JP3.5, R63.2
unnamed: JP3.7, R64.2
unnamed: C38.1, U3.23 (COMP2)
unnamed: R110.2, U2.79 (PD10)
unnamed: IC1.4 (DO), R83.1, R146.2
unnamed: R112.2, U2.80 (PD11)
unnamed: D3.A, R114.1
unnamed: R113.2, U2.81 (PD12)
unnamed: R114.2, U2.82 (PD13)
unnamed: D2.A, R113.1
unnamed: C39.1, U3.19 (COMP1)
unnamed: D4.A, R112.1
unnamed: D5.A, R110.1
unnamed: R138.2, U42.M9 (M0_0)
unnamed: R139.2, U42.M10 (M1_0)
unnamed: R140.2, U42.M11 (M2_0)
unnamed: R141.2, U42.L9 (PROGRAM_B_0)
unnamed: R142.2, U42.E7 (CFGBVS_0)
unnamed: R144.1, U42.H10 (DONE_0)
unnamed: R143.1, U42.K10 (INIT_B_0)
unnamed: R60.1, U6.6 (REF)
unnamed: C184.1, U6.2 (OSCI), Y1.P1 (1)
unnamed: C185.1, U6.3 (OSCO), Y1.P3 (2)
unnamed: C186.A (+), C188.2, L20.1, U6.9 (VPLL)
unnamed: C187.A (+), C189.1, L19.1, U6.4 (VPHY)
unnamed: IC1.1 (CS), R145.1, U6.63 (EECS)
unnamed: IC1.2 (SK), R84.1, U6.62 (EECLK)
unnamed: IC1.3 (DI), R146.1, U6.61 (EEDATA)
RX_2: TP17.1, U2.37 (PA3)
SI5351_CLK0: U10.13 (CLK0)
SI5351_CLK1: U10.12 (CLK1)
SI5351_CLK2: U10.9 (CLK2)
SI5351_CLK3: U10.8 (CLK3)
SI5351_CLK4: U10.19 (CLK4), U42.N11 (IO_L13P_T2_MRCC_14)
SI5351_CLK5: U10.17 (CLK5)
SI5351_CLK6: U10.16 (CLK6); also elsewhere on the board
SI5351_CLK7: U10.15 (CLK7)
SI5351_CLOCKS_EN: R19.1, U2.134 (PB4), U10.7 (OEB)
SI5351_SS_EN: R20.1, U2.135 (PB5), U10.6 (SSEN)
STM32_MISO: U2.42 (PA6), U42.G14 (IO_L21P_T3_DQS_15); also elsewhere on the board
STM32_MISO_1V8: U42.A5 (IO_L3P_T0_DQS_AD5P_35); also elsewhere on the board
STM32_MOSI: U2.43 (PA7), U42.H13 (IO_L20N_T3_A19_15); also elsewhere on the board
STM32_MOSI_1V8: U42.B5 (IO_L2N_T0_AD12N_35); also elsewhere on the board
STM32_NRST: C164.2, JP2.5, R111.1, S1.3 (2), S1.4 (2), U2.25 (NRST)
STM32_OSC_32N: C18.1, U2.8 (PC14), XTAL3.2
STM32_OSC_32P: C19.1, U2.9 (PC15), XTAL3.1
STM32_OSC_N: C20.1, U2.23 (PH0), XTAL1.2
STM32_OSC_P: C21.1, U2.24 (PH1), XTAL1.1
STM32_SCL1: JP5.3, R21.1, U2.136 (PB6), U10.4 (SCL)
STM32_SCLK: U2.41 (PA5), U42.E12 (IO_L13P_T2_MRCC_15); also elsewhere on the board
STM32_SCLK_1V8: U42.F5 (IO_L13P_T2_MRCC_35); also elsewhere on the board
STM32_SDA1: JP5.2, R22.1, U2.137 (PB7), U10.5 (SDA)
STM32_SWCLK: JP2.2, U2.109 (PA14)
STM32_SWDIO: JP2.4, U2.105 (PA13)
STM32_SWO: JP2.6, U2.133 (PB3)
TX_2: TP16.1, U2.36 (PA2)

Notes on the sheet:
DIGITAL (FPGA + MICROCONTROLLER) + ADC & DAC

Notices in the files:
README.md:
Hardware: CERN-OHL-P
parts and their libraries:
SparkFun-LED: Licensing: Creative Commons ShareAlike 4.0 International - https://creativecommons.org/licenses/by-sa/4.0
Eagle_WR-SMP_rev21a: Copyright: Würth Elektronik
COPYRIGHT: Copyright (C) 2024 Ultra Librarian. All rights reserved.
